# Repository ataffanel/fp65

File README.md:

# FP65: 65C02-based experimental computer platform

FP65 is a modular (retro)computer project based on the WDC65C02s.
It is mainly a playground to play and experiments with old computer technology and chips.

The design is modular in the sense that it is based on a backplane that carries the 65C02 memory bus.

The `FP` of *FP65* stands for *Front Panel*.
The original idea of the project is to build a front-panel controlable computer based on the 65C02.
Something very similar to the Altair 8800 or the IMSAI 8080.
The project has been a little bit side-tracked so far, but this is still one of the goal.

## Project goals and limitations

The main goal is to have fun with old computer technologies, learning new skils in the process in a nice side-effect.
In order to keep things fun and interesting, there needs to be some (artificial) limitations.

The focus so far has been to make a retro-inspired computer platform only using through-hole components that are still readily available (as of late 2023) at regular electronic retailer.
I could have sourced cool parts from ebay (and I am entertaining the idea for doing a 68K-based project), but here I really wanted to stick with easily and safely sourcable parts.
The only exception to this rule is the [USBIO-A](usbio-a/) board that uses an Arduino board to essencially emulate an Apple I keyboard and screen to USB-serial.

Within this focus, the spread of chip and design vintage is quite big: the modular backbone design is inspired by the later 70s computer kit like the Altair 8800 and the IMSAI 8080.
The main CPU, the WDC65C02s, is an improved CMOS version of the MOS6502 from the 80s. Similarly the SCSI-A 53C80 SCSI chip has its roots in the mid-80s.

The latest technologies so far are found in the SIO-A board that uses a 16C550 UART tranceiver, this chips is a late-80s chip but is very much reminecent of the 90s and early 2000s PC technology.
chance are, your current PC-compatible computer still has a 16550-compatible UART somewhere in the chipset.

Of course the memory used, be it static RAM or ROM (actually a FLASH chip), are also 90s to 2000s technologies: they are the latest generation still available as through-hole components.

## Boards

The board made so far are:
 - [Backplane](backplane/): 50-pins 4 boards backplane with power supply and chaining connectors
 - [MPU-A](mpu-a/): wdc65C02s CPU board with clock
 - [RAM-A](ram-a/): 32KBytes static ram
 - [ROM-A](rom-a/): 4KBytes to 24KBytes ROM. Implemented in a 128KBytes FLASH with 8 static pages (dip-switch selectable).
 - [SCSI-A](scsi-a/): Asynchronous 8bit SCSI-SC interface. SCSI2 compatible with internal and external MAC-style connector.
 - [SIO-A](sio-a/): 16C550 UART with RS232-level and TTS-level connection plus 65C22 VIA for Timer and parallel (GP)I/O
 - [USBIO-A](usbio-a/): APPLE-I style emulated I/O to a USB-serial port.

Most boards have been revised since the rev-A was produced.
Rev-Bs are implementation of the bodge wires fixes, they still need to be produced and tested.

# Software

FP65 has a memory map and I/O compatible with an apple-I (when using the USBIO-A board).
As such it can run WOZMON, the apple-I monitor, and any apple-I/replica-I software directly.

# License

All the board in this repos are licenced under the *CERN Open Hardware Licence Version 2 - Strongly Reciprocal* (CERN-OHL-S) license.

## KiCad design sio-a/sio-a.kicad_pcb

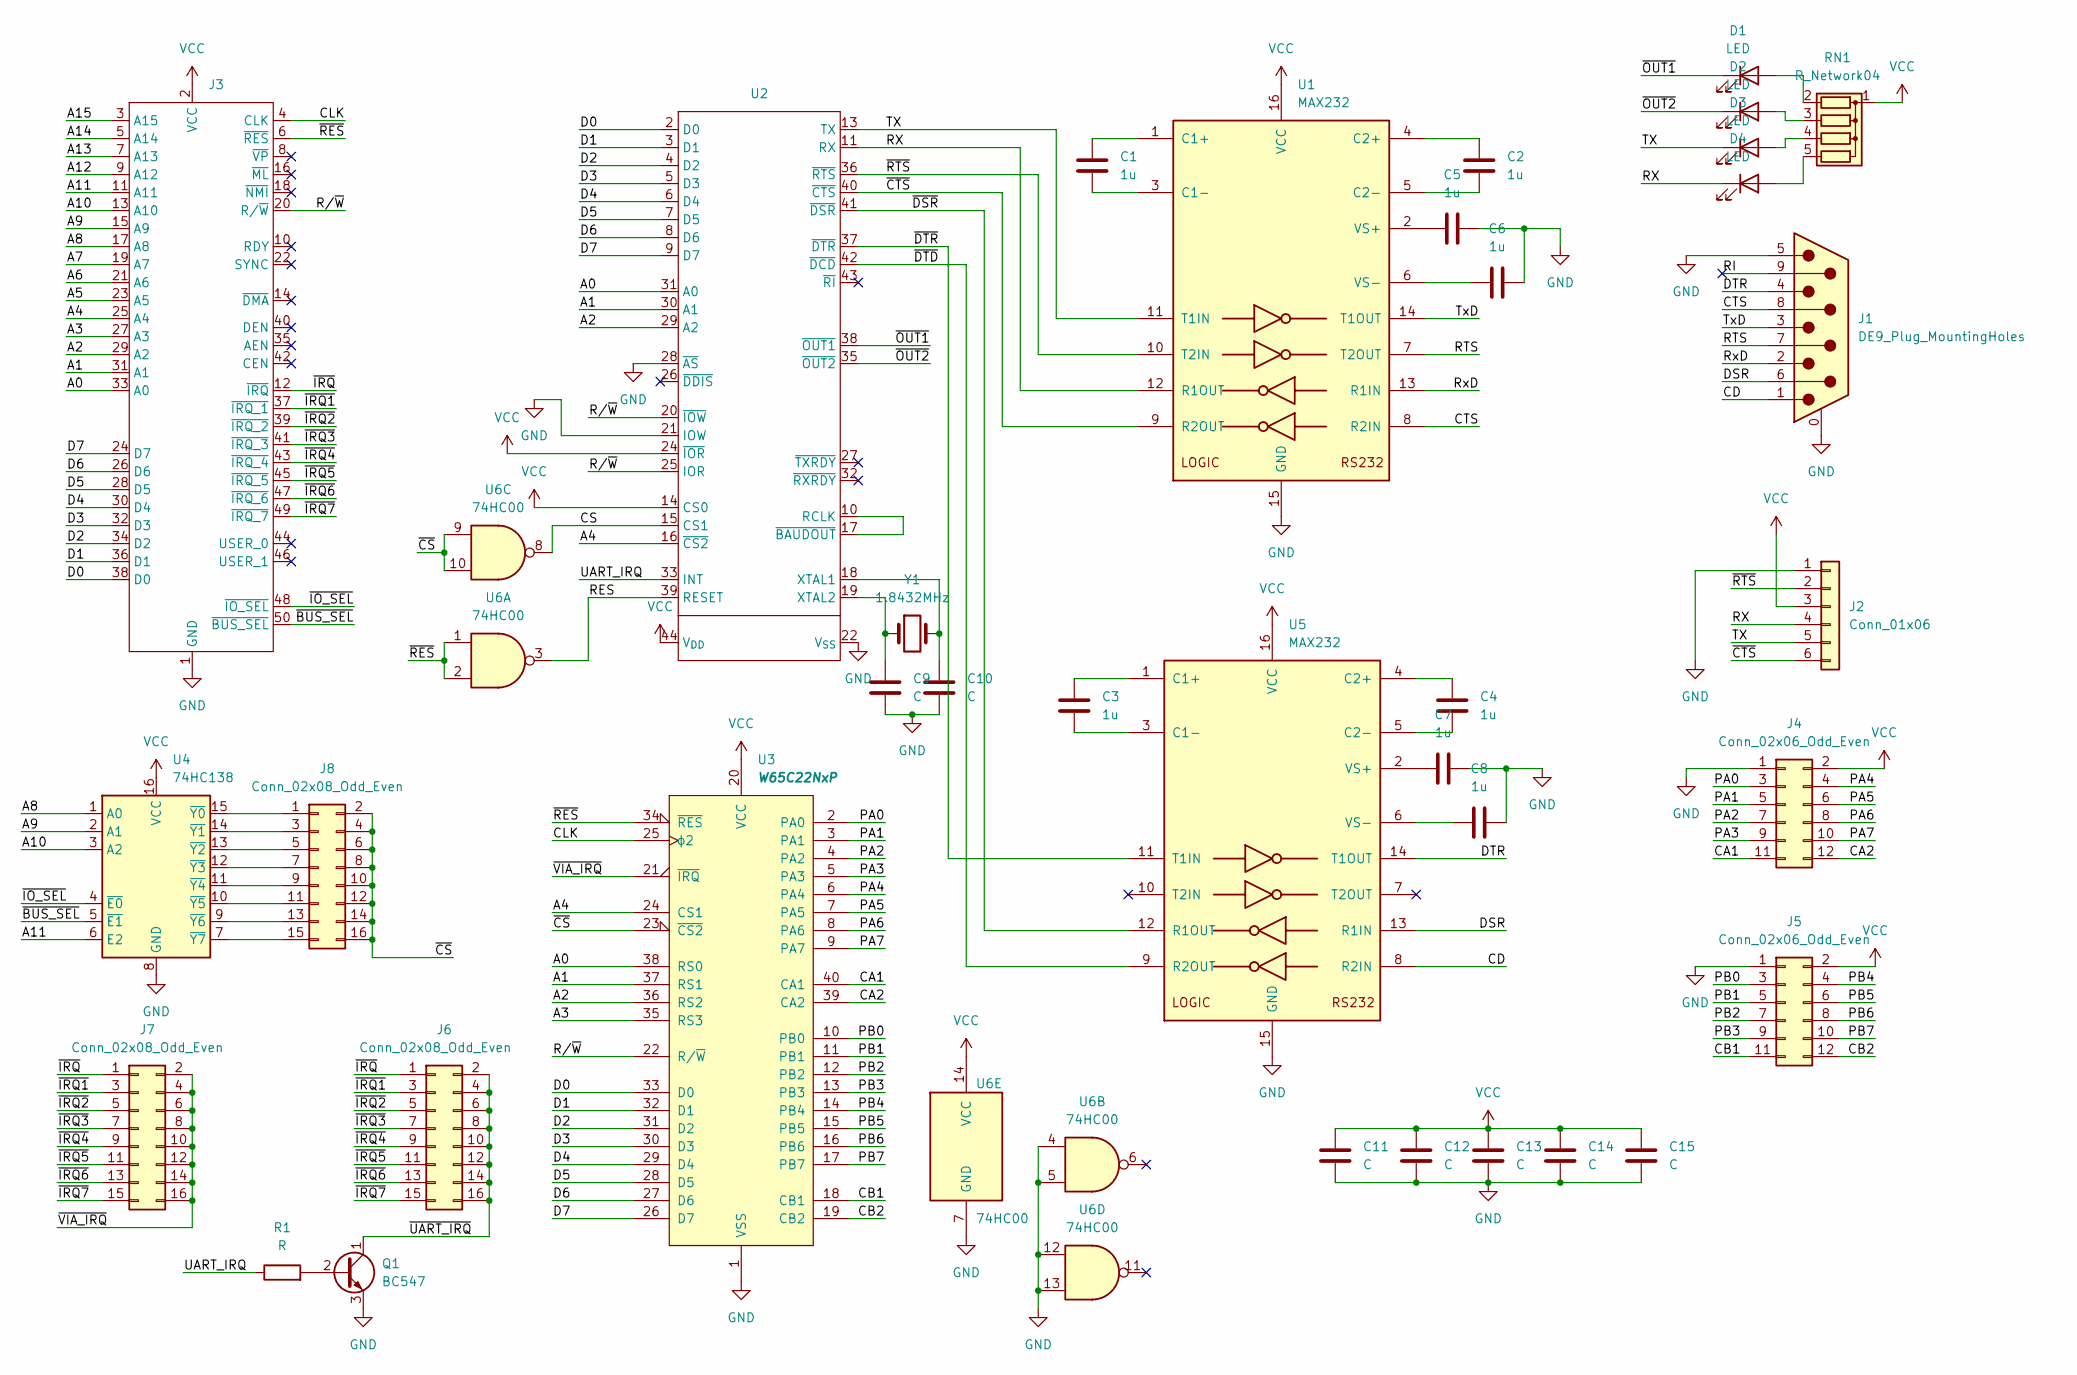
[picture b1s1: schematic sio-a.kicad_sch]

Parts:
C1, C2, C3, C4, C5, C6, C7, C8: 1u; C_Disc_D5.0mm_W2.5mm_P5.00mm
C9, C10, C11, C12, C13, C14, C15: C; C_Disc_D5.0mm_W2.5mm_P5.00mm
D1, D2, D3, D4: LED; LED_D3.0mm_Horizontal_O1.27mm_Z2.0mm
J1: DE9_Plug_MountingHoles; DSUB-9_Male_Horizontal_P2.77x2.84mm_EdgePinOffset9.90mm_Hou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
J2: Conn_01x06; PinHeader_1x06_P2.54mm_Horizontal
J3: PinHeader_2x25_P2.54mm_Horizontal
J4, J5: Conn_02x06_Odd_Even; PinHeader_2x06_P2.54mm_Vertical
J6, J7, J8: Conn_02x08_Odd_Even; PinHeader_2x08_P2.54mm_Vertical
Q1: BC547; TO-92_Inline
R1: R; R_Axial_DIN0207_L6.3mm_D2.5mm_P10.16mm_Horizontal
RN1: R_Network04; R_Array_SIP5
U1, U5: MAX232; DIP-16_W7.62mm
U2: PLCC-44_THT-Socket
U3: W65C22NxP; DIP-40_W15.24mm
U4: 74HC138; DIP-16_W7.62mm
U6: 74HC00; DIP-14_W7.62mm
Y1: 1.8432MHz; Crystal_HC49-U_Vertical

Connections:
/A0: J3.33 (A0), U2.31 (A0), U3.38 (RS0)
/A1: J3.31 (A1), U2.30 (A1), U3.37 (RS1)
/A2: J3.29 (A2), U2.29 (A2), U3.36 (RS2)
/A3: J3.27 (A3), U3.35 (RS3)
/A4: J3.25 (A4), U2.16 (~CS2), U3.24 (CS1)
/A5: J3.23 (A5)
/A6: J3.21 (A6)
/A7: J3.19 (A7)
/A8: J3.17 (A8), U4.1 (A0)
/A9: J3.15 (A9), U4.2 (A1)
/A10: J3.13 (A10), U4.3 (A2)
/A11: J3.11 (A11), U4.6 (E2)
/A12: J3.9 (A12)
/A13: J3.7 (A13)
/A14: J3.5 (A14)
/A15: J3.3 (A15)
/CA1: J4.11, U3.40 (CA1)
/CA2: J4.12, U3.39 (CA2)
/CB1: J5.11, U3.18 (CB1)
/CB2: J5.12, U3.19 (CB2)
/CD: J1.1, U5.8 (R2IN)
/CLK: J3.4 (CLK), U3.25 (ϕ2)
/CS: U2.15 (CS1), U6.8
/CTS: J1.8, U1.8 (R2IN)
/D0: J3.38 (D0), U2.2 (D0), U3.33 (D0)
/D1: J3.36 (D1), U2.3 (D1), U3.32 (D1)
/D2: J3.34 (D2), U2.4 (D2), U3.31 (D2)
/D3: J3.32 (D3), U2.5 (D3), U3.30 (D3)
/D4: J3.30 (D4), U2.6 (D4), U3.29 (D4)
/D5: J3.28 (D5), U2.7 (D5), U3.28 (D5)
/D6: J3.26 (D6), U2.8 (D6), U3.27 (D6)
/D7: J3.24 (D7), U2.9 (D7), U3.26 (D7)
/DSR: J1.6, U5.13 (R1IN)
/DTR: J1.4, U5.14 (T1OUT)
/PA0: J4.3, U3.2 (PA0)
/PA1: J4.5, U3.3 (PA1)
/PA2: J4.7, U3.4 (PA2)
/PA3: J4.9, U3.5 (PA3)
/PA4: J4.4, U3.6 (PA4)
/PA5: J4.6, U3.7 (PA5)
/PA6: J4.8, U3.8 (PA6)
/PA7: J4.10, U3.9 (PA7)
/PB0: J5.3, U3.10 (PB0)
/PB1: J5.5, U3.11 (PB1)
/PB2: J5.7, U3.12 (PB2)
/PB3: J5.9, U3.13 (PB3)
/PB4: J5.4, U3.14 (PB4)
/PB5: J5.6, U3.15 (PB5)
/PB6: J5.8, U3.16 (PB6)
/PB7: J5.10, U3.17 (PB7)
/RES: U2.39 (RESET), U6.3
/RI: J1.9
/RTS: J1.7, U1.7 (T2OUT)
/RX: D4.1 (K), J2.4, U1.12 (R1OUT), U2.11 (RX)
/RxD: J1.2, U1.13 (R1IN)
/R/~W: J3.20 (R/~W), U2.20 (~IOW), U2.25 (IOR), U3.22 (R/~W)
/TX: D3.1 (K), J2.5, U1.11 (T1IN), U2.13 (TX)
/TxD: J1.3, U1.14 (T1OUT)
/UART_IRQ: R1.1, U2.33 (INT)
/~BUS_SEL: J3.50 (~BUS_SEL), U4.5 (~E1)
/~CS: J8.2, J8.4, J8.6, J8.8, J8.10, J8.12, J8.14, J8.16, U3.23 (~CS2), U6.9, U6.10
/~CTS: J2.6, U1.9 (R2OUT), U2.40 (~CTS)
/~DSR: U2.41 (~DSR), U5.12 (R1OUT)
/~DTD: U2.42 (~DCD), U5.9 (R2OUT)
/~DTR: U2.37 (~DTR), U5.11 (T1IN)
/~IO_SEL: J3.48 (~IO_SEL), U4.4 (~E0)
/~IRQ1: J3.37 (~IRQ_1), J6.3, J7.3
/~IRQ2: J3.39 (~IRQ_2), J6.5, J7.5
/~IRQ3: J3.41 (~IRQ_3), J6.7, J7.7
/~IRQ4: J3.43 (~IRQ_4), J6.9, J7.9
/~IRQ5: J3.45 (~IRQ_5), J6.11, J7.11
/~IRQ6: J3.47 (~IRQ_6), J6.13, J7.13
/~IRQ7: J3.49 (~IRQ_7), J6.15, J7.15
/~IRQ: J3.12 (~IRQ), J6.1, J7.1
/~OUT1: D1.1 (K), U2.38 (~OUT1)
/~OUT2: D2.1 (K), U2.35 (~OUT2)
/~RES: J3.6 (~RES), U3.34 (~RES), U6.1, U6.2
/~RTS: J2.2, U1.10 (T2IN), U2.36 (~RTS)
/~UART_IRQ: J6.2, J6.4, J6.6, J6.8, J6.10, J6.12, J6.14, J6.16, Q1.1 (C)
/~VIA_IRQ: J7.2, J7.4, J7.6, J7.8, J7.10, J7.12, J7.14, J7.16, U3.21 (~IRQ)
GND: C5.2, C6.2, C7.1, C8.2, C9.2, C10.2, C11.2, C12.2, C13.2, C14.2, C15.2, J1.0 (PAD), J1.5, J2.1, J3.1 (GND), J4.1, J5.1, Q1.3 (E), U1.15 (GND), U2.21 (IOW), U2.22 (V_{SS}), U2.28 (~AS), U3.1 (VSS), U4.8 (GND), U5.15 (GND), U6.4, U6.5, U6.7 (GND), U6.12, U6.13
unnamed: D1.2 (A), RN1.2 (R1)
unnamed: D2.2 (A), RN1.3 (R2)
unnamed: D3.2 (A), RN1.4 (R3)
unnamed: D4.2 (A), RN1.5 (R4)
unnamed: J8.1, U4.15 (~Y0)
unnamed: J8.3, U4.14 (~Y1)
unnamed: J8.5, U4.13 (~Y2)
unnamed: J8.7, U4.12 (~Y3)
unnamed: J8.9, U4.11 (~Y4)
unnamed: J8.11, U4.10 (~Y5)
unnamed: J8.13, U4.9 (~Y6)
unnamed: J8.15, U4.7 (~Y7)
unnamed: Q1.2 (B), R1.2
unnamed: C1.1, U1.1 (C1+)
unnamed: C1.2, U1.3 (C1-)
unnamed: C2.1, U1.4 (C2+)
unnamed: C2.2, U1.5 (C2-)
unnamed: C5.1, U1.2 (VS+)
unnamed: C6.1, U1.6 (VS-)
unnamed: U2.10 (RCLK), U2.17 (~BAUDOUT)
unnamed: C10.1, U2.18 (XTAL1), Y1.2
unnamed: C9.1, U2.19 (XTAL2), Y1.1
unnamed: C3.1, U5.1 (C1+)
unnamed: C3.2, U5.3 (C1-)
unnamed: C4.1, U5.4 (C2+)
unnamed: C4.2, U5.5 (C2-)
unnamed: C7.2, U5.2 (VS+)
unnamed: C8.1, U5.6 (VS-)
VCC: C11.1, C12.1, C13.1, C14.1, C15.1, J2.3, J3.2 (VCC), J4.2, J5.2, RN1.1 (common), U1.16 (VCC), U2.14 (CS0), U2.24 (~IOR), U2.44 (V_{DD}), U3.20 (VCC), U4.16 (VCC), U5.16 (VCC), U6.14 (VCC)

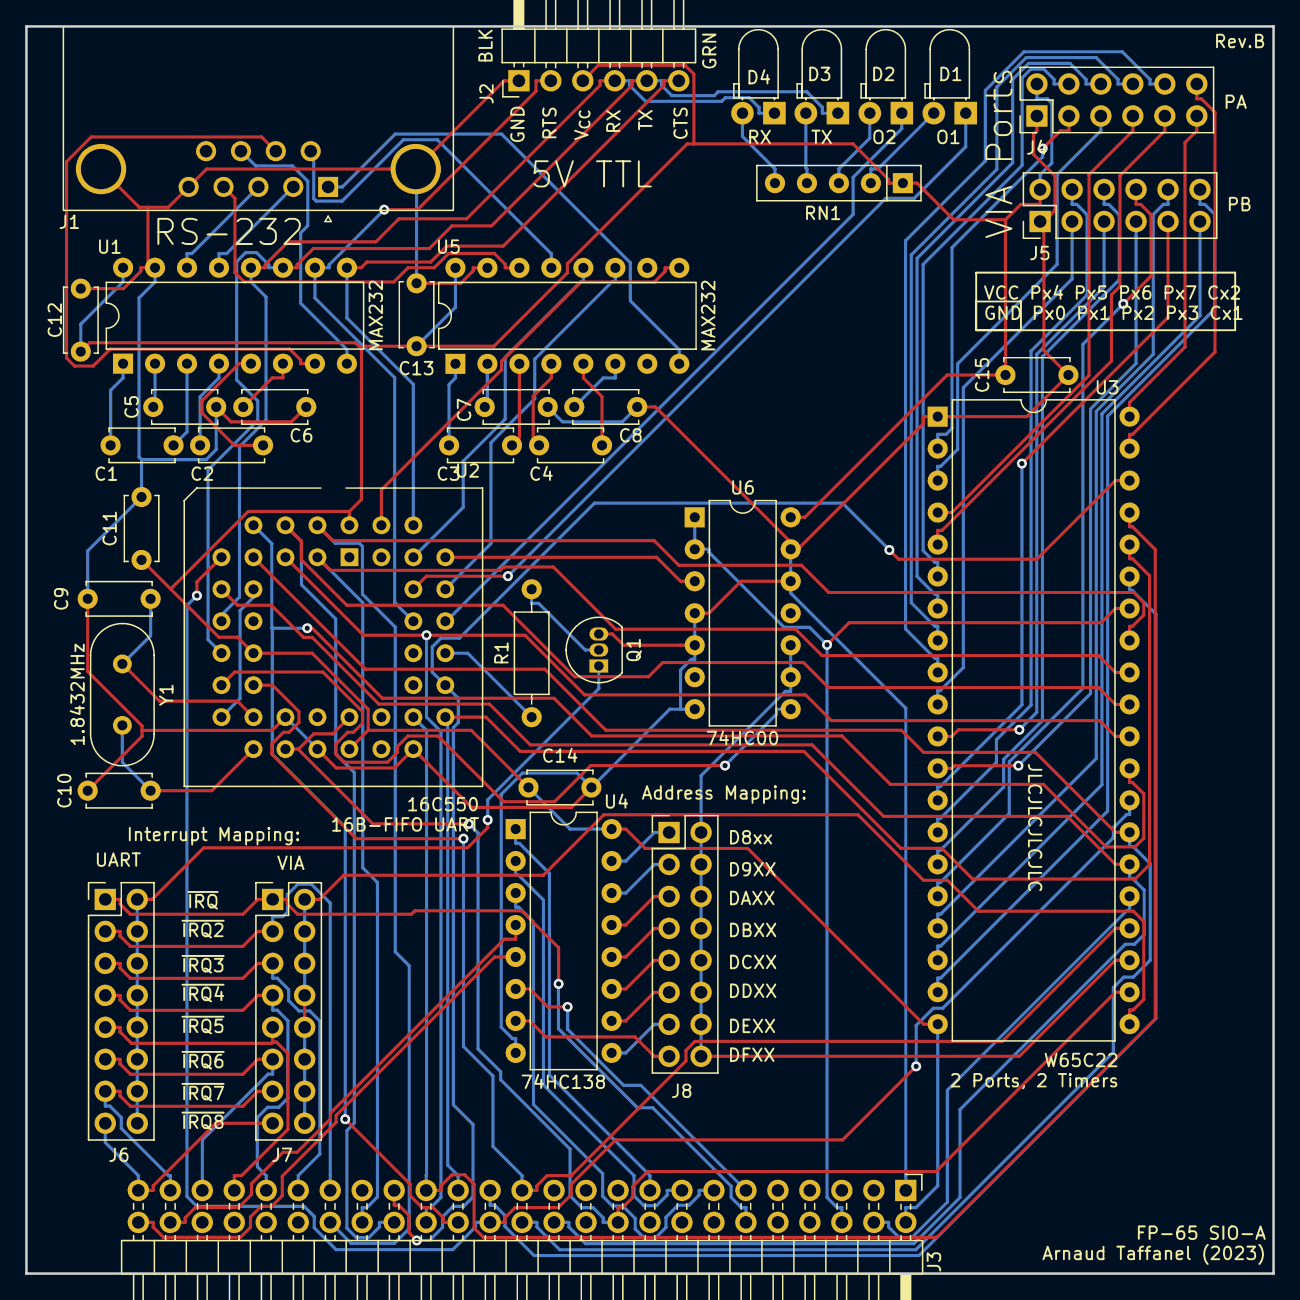
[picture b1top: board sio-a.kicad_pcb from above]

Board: 2 copper layers, 99.1 x 99.1 mm, 37 parts (0 on the bottom side), 102 nets.

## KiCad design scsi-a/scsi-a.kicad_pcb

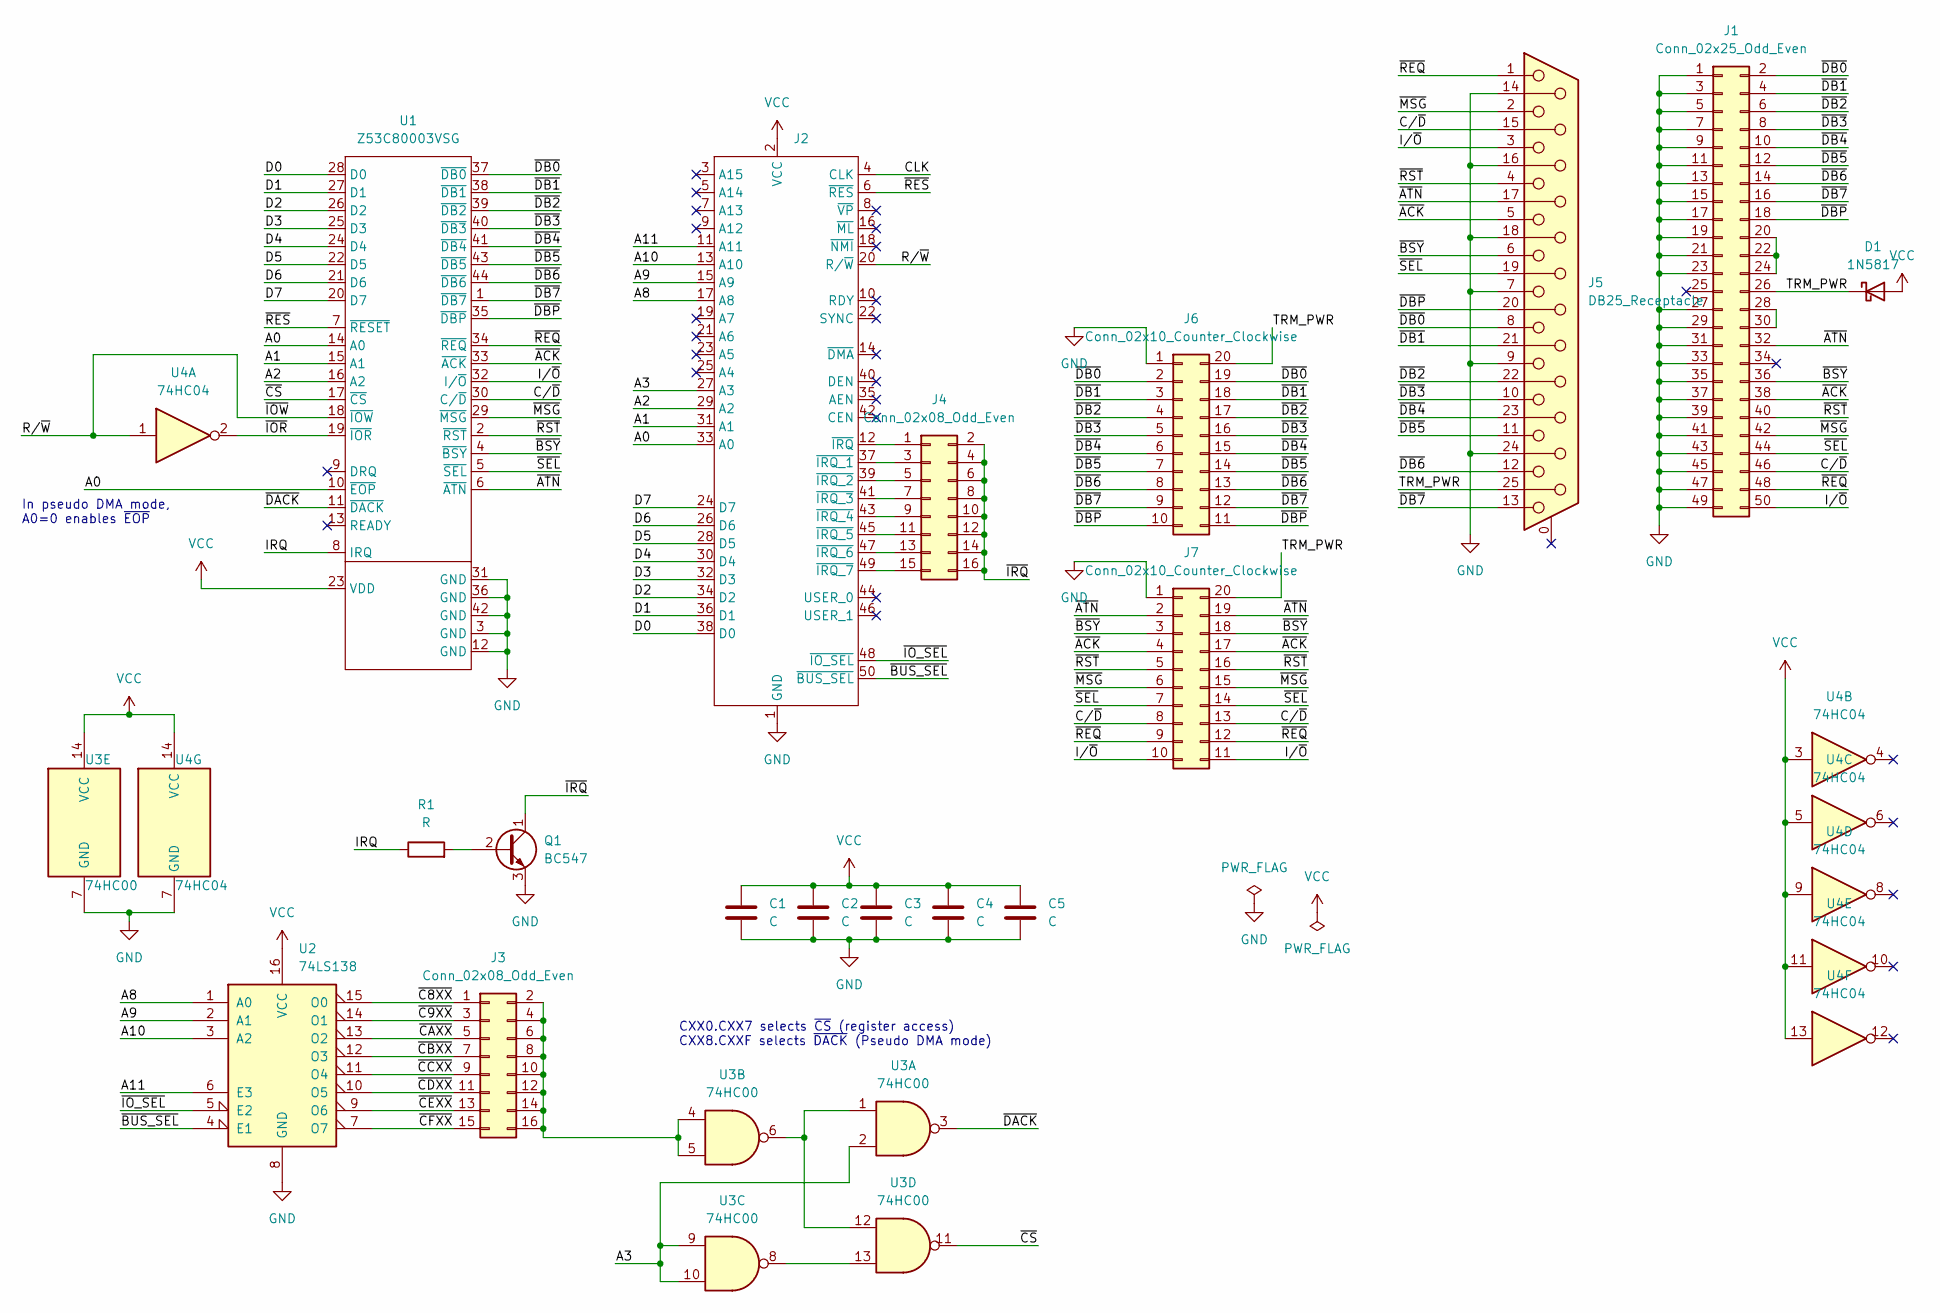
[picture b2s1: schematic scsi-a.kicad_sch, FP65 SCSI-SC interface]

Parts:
C1, C2, C3, C5: C; C_Disc_D5.0mm_W2.5mm_P5.00mm
C4: C; CP_Radial_D5.0mm_P2.00mm
D1: 1N5817; D_DO-41_SOD81_P10.16mm_Horizontal
J1: Conn_02x25_Odd_Even; IDC-Header_2x25_P2.54mm_Horizontal
J2: PinHeader_2x25_P2.54mm_Horizontal
J3, J4: Conn_02x08_Odd_Even; PinHeader_2x08_P2.54mm_Vertical
J5: DB25_Receptacle; DSUB-25_Female_Horizontal_P2.77x2.84mm_EdgePinOffset9.90mm_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
J6, J7: Conn_02x10_Counter_Clockwise; DIP-20_W7.62mm_Socket
Q1: BC547; TO-92_Inline
R1: R; R_Axial_DIN0204_L3.6mm_D1.6mm_P7.62mm_Horizontal
U1: Z53C80003VSG; PLCC-44_THT-Socket
U2: 74LS138; DIP-16_W7.62mm
U3: 74HC00; DIP-14_W7.62mm
U4: 74HC04; DIP-14_W7.62mm

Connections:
/A0: J2.33 (A0), U1.10 (~EOP), U1.14 (A0)
/A1: J2.31 (A1), U1.15 (A1)
/A2: J2.29 (A2), U1.16 (A2)
/A3: J2.27 (A3), U3.2, U3.9, U3.10
/A8: J2.17 (A8), U2.1 (A0)
/A9: J2.15 (A9), U2.2 (A1)
/A10: J2.13 (A10), U2.3 (A2)
/A11: J2.11 (A11), U2.6 (E3)
/CLK: J2.4 (CLK)
/C/~D: J1.46, J5.15, J7.8, J7.13, U1.30 (C/~D)
/D0: J2.38 (D0), U1.28 (D0)
/D1: J2.36 (D1), U1.27 (D1)
/D2: J2.34 (D2), U1.26 (D2)
/D3: J2.32 (D3), U1.25 (D3)
/D4: J2.30 (D4), U1.24 (D4)
/D5: J2.28 (D5), U1.22 (D5)
/D6: J2.26 (D6), U1.21 (D6)
/D7: J2.24 (D7), U1.20 (D7)
/IRQ: R1.1, U1.8 (IRQ)
/I/~O: J1.50, J5.3, J7.10, J7.11, U1.32 (I/~O)
/R/~W: J2.20 (R/~W), U1.18 (~IOW), U4.1
/TRM_PWR: D1.1 (K), J1.26, J5.25, J6.20, J7.20
/~ACK: J1.38, J5.5, J7.4, J7.17, U1.33 (~ACK)
/~ATN: J1.32, J5.17, J7.2, J7.19, U1.6 (~ATN)
/~BSY: J1.36, J5.6, J7.3, J7.18, U1.4 (~BSY)
/~BUS_SEL: J2.50 (~BUS_SEL), U2.4 (E1)
/~C8XX: J3.1, U2.15 (O0)
/~C9XX: J3.3, U2.14 (O1)
/~CAXX: J3.5, U2.13 (O2)
/~CBXX: J3.7, U2.12 (O3)
/~CCXX: J3.9, U2.11 (O4)
/~CDXX: J3.11, U2.10 (O5)
/~CEXX: J3.13, U2.9 (O6)
/~CFXX: J3.15, U2.7 (O7)
/~CS: U1.17 (~CS), U3.11
/~DACK: U1.11 (~DACK), U3.3
/~DB0: J1.2, J5.8, J6.2, J6.19, U1.37 (~DB0)
/~DB1: J1.4, J5.21, J6.3, J6.18, U1.38 (~DB1)
/~DB2: J1.6, J5.22, J6.4, J6.17, U1.39 (~DB2)
/~DB3: J1.8, J5.10, J6.5, J6.16, U1.40 (~DB3)
/~DB4: J1.10, J5.23, J6.6, J6.15, U1.41 (~DB4)
/~DB5: J1.12, J5.11, J6.7, J6.14, U1.43 (~DB5)
/~DB6: J1.14, J5.12, J6.8, J6.13, U1.44 (~DB6)
/~DB7: J1.16, J5.13, J6.9, J6.12, U1.1 (~DB7)
/~DBP: J1.18, J5.20, J6.10, J6.11, U1.35 (~DBP)
/~IOR: U1.19 (~IOR), U4.2
/~IO_SEL: J2.48 (~IO_SEL), U2.5 (E2)
/~IRQ: J4.2, J4.4, J4.6, J4.8, J4.10, J4.12, J4.14, J4.16, Q1.1 (C)
/~MSG: J1.42, J5.2, J7.6, J7.15, U1.29 (~MSG)
/~REQ: J1.48, J5.1, J7.9, J7.12, U1.34 (~REQ)
/~RES: J2.6 (~RES), U1.7 (~RESET)
/~RST: J1.40, J5.4, J7.5, J7.16, U1.2 (~RST)
/~SEL: J1.44, J5.19, J7.7, J7.14, U1.5 (~SEL)
GND: C1.2, C2.2, C3.2, C4.2, C5.2, J1.1, J1.3, J1.5, J1.7, J1.9, J1.11, J1.13, J1.15, J1.17, J1.19, J1.21, J1.23, J1.27, J1.29, J1.31, J1.33, J1.35, J1.37, J1.39, J1.41, J1.43, J1.45, J1.47, J1.49, J2.1 (GND), J5.7, J5.9, J5.14, J5.16, J5.18, J5.24, J6.1, J7.1, Q1.3 (E), U1.3 (GND), U1.12 (GND), U1.31 (GND), U1.36 (GND), U1.42 (GND), U2.8 (GND), U3.7 (GND), U4.7 (GND)
unnamed: J1.20, J1.22, J1.24
unnamed: J1.28, J1.30
unnamed: J2.37 (~IRQ_1), J4.3
unnamed: J2.39 (~IRQ_2), J4.5
unnamed: J2.41 (~IRQ_3), J4.7
unnamed: J2.43 (~IRQ_4), J4.9
unnamed: J2.45 (~IRQ_5), J4.11
unnamed: J2.47 (~IRQ_6), J4.13
unnamed: J2.49 (~IRQ_7), J4.15
unnamed: J2.12 (~IRQ), J4.1
unnamed: J3.2, J3.4, J3.6, J3.8, J3.10, J3.12, J3.14, J3.16, U3.4, U3.5
unnamed: Q1.2 (B), R1.2
unnamed: U3.1, U3.6, U3.12
unnamed: U3.8, U3.13
VCC: C1.1, C2.1, C3.1, C4.1, C5.1, D1.2 (A), J2.2 (VCC), U1.23 (VDD), U2.16 (VCC), U3.14 (VCC), U4.3, U4.5, U4.9, U4.11, U4.13, U4.14 (VCC)

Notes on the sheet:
CXX0.CXX7 selects ~{CS} (register access) CXX8.CXXF selects ~{DACK} (Pseudo DMA mode)
In pseudo DMA mode, A0=0 enables ~{EOP}

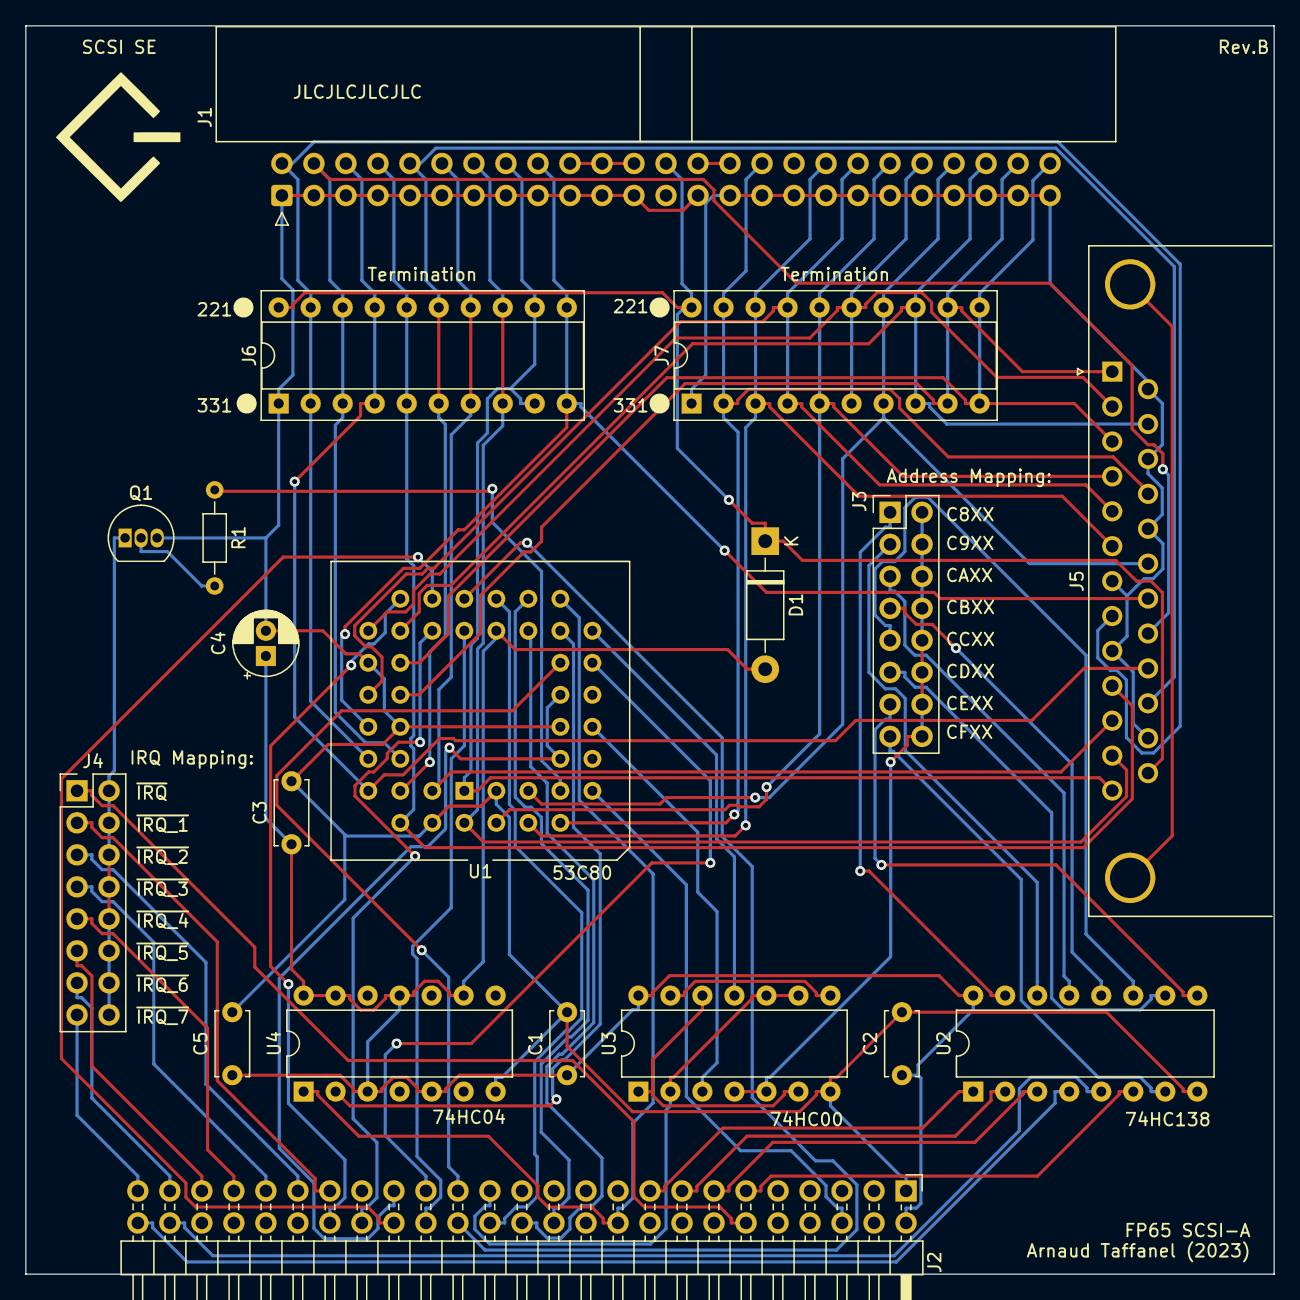
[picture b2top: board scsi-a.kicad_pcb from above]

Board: 2 copper layers, 99.1 x 99.1 mm, 19 parts (0 on the bottom side), 68 nets.

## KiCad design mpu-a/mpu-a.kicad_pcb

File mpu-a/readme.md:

# wdc65C02s CPU board with clock

CPU board for the 65C02.

Implements support for a crystall oscillator and connector and logic for a front-pannel to access the CPU data line even when isolated from the backplane.

Also generates an enable signal for selecting the IO pages at ```$Cxxx```.

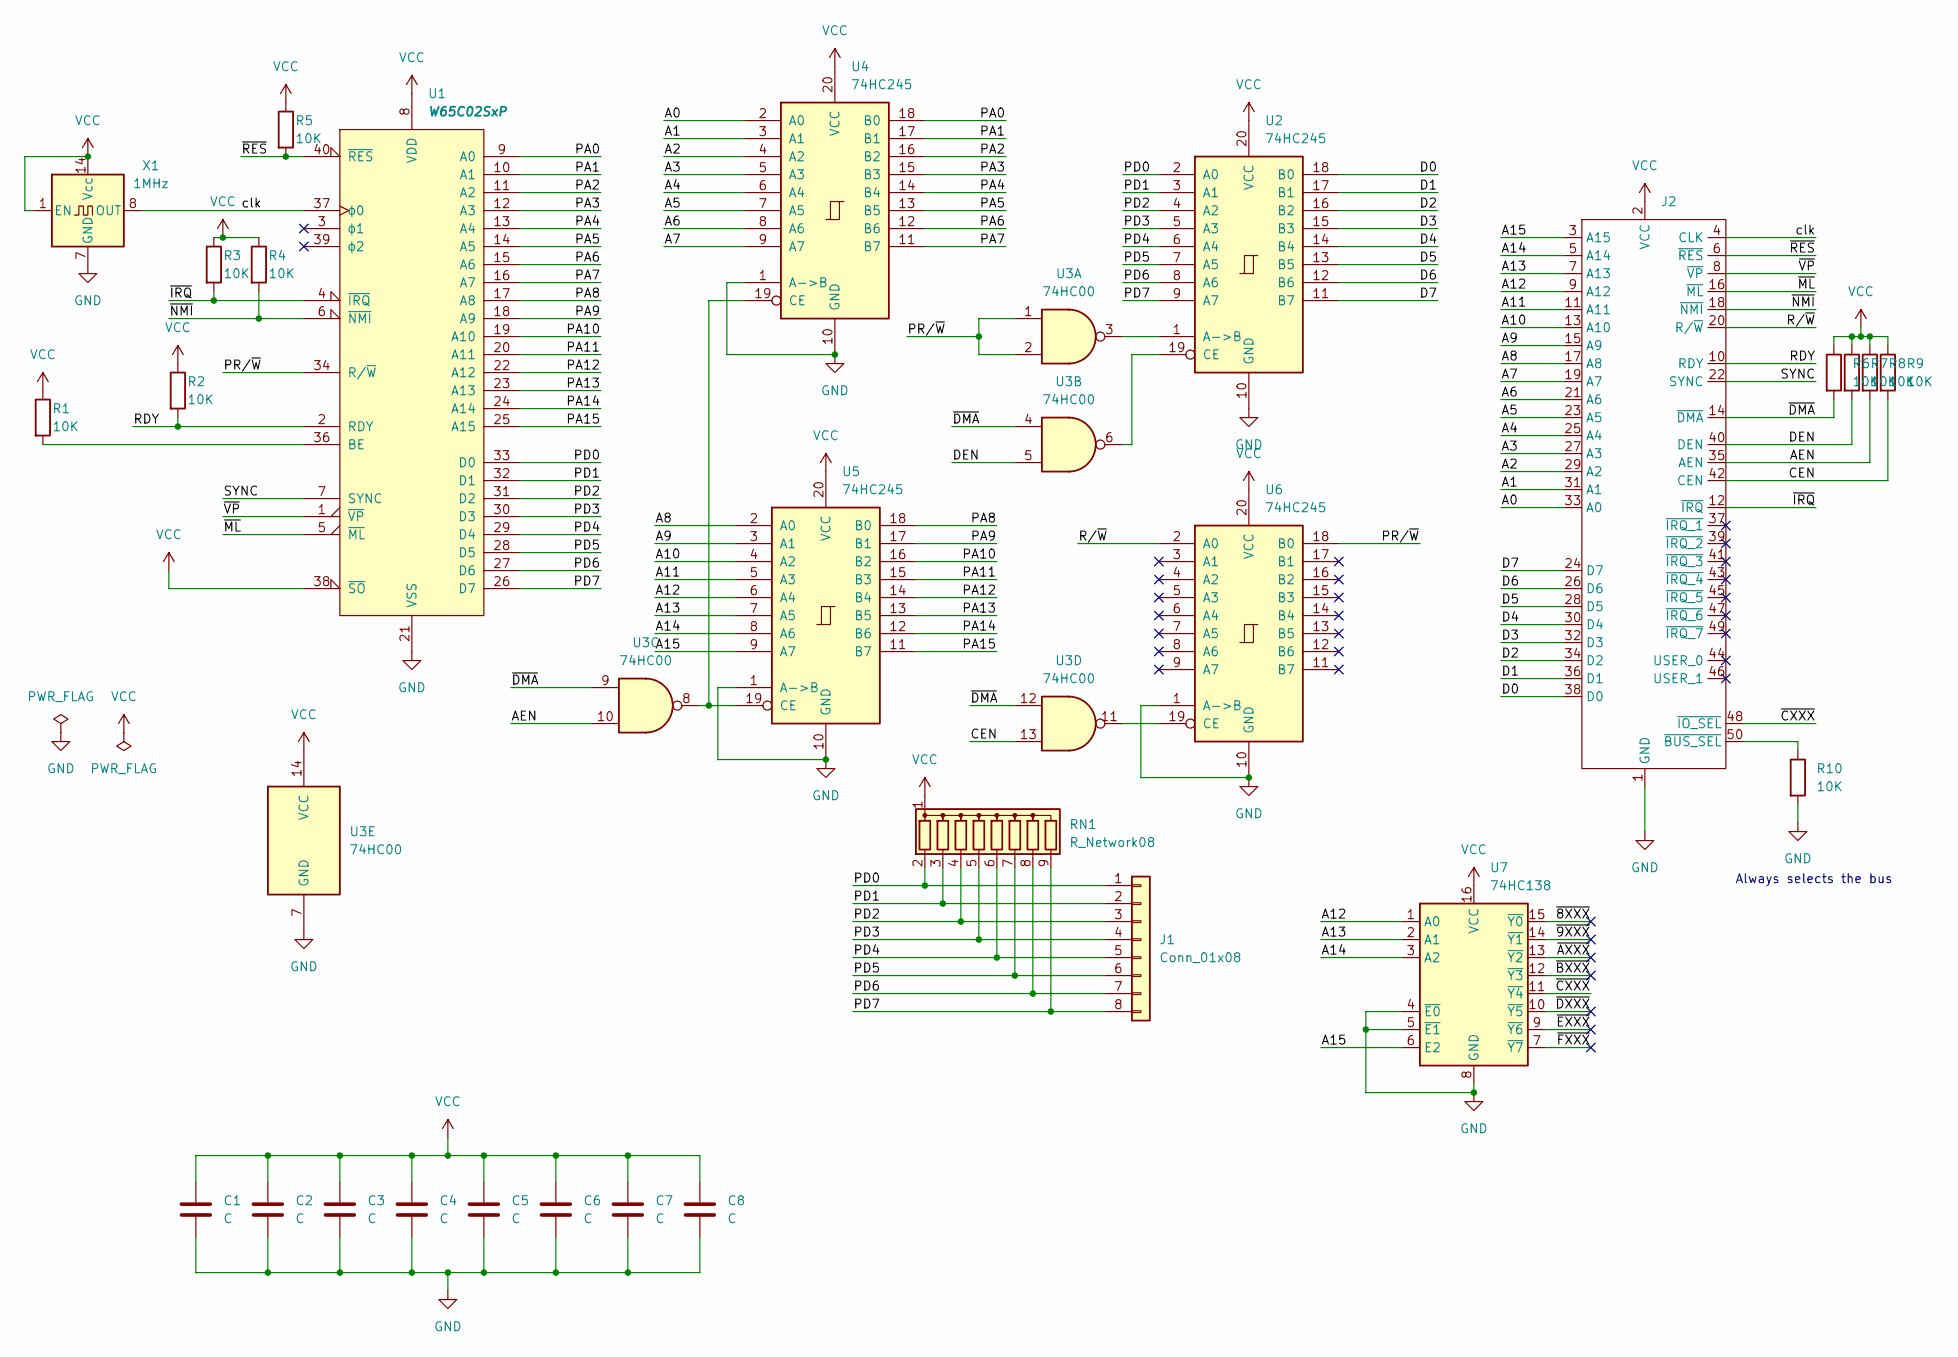
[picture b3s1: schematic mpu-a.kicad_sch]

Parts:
C1, C2, C3, C4, C5, C6, C7, C8: C; C_Disc_D4.3mm_W1.9mm_P5.00mm
J1: Conn_01x08; PinHeader_2x04_P2.54mm_Vertical
J2: PinHeader_2x25_P2.54mm_Horizontal
R1, R2, R3, R4, R5, R6, R7, R8, R9, R10: 10K; R_Axial_DIN0204_L3.6mm_D1.6mm_P7.62mm_Horizontal
RN1: R_Network08; R_Array_SIP9
U1: W65C02SxP; DIP-40_W15.24mm
U2, U4, U5, U6: 74HC245; DIP-20_W7.62mm
U3: 74HC00; DIP-14_W7.62mm
U7: 74HC138; DIP-16_W7.62mm
X1: 1MHz; Oscillator_DIP-14

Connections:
/A0: J2.33 (A0), U4.2 (A0)
/A1: J2.31 (A1), U4.3 (A1)
/A2: J2.29 (A2), U4.4 (A2)
/A3: J2.27 (A3), U4.5 (A3)
/A4: J2.25 (A4), U4.6 (A4)
/A5: J2.23 (A5), U4.7 (A5)
/A6: J2.21 (A6), U4.8 (A6)
/A7: J2.19 (A7), U4.9 (A7)
/A8: J2.17 (A8), U5.2 (A0)
/A9: J2.15 (A9), U5.3 (A1)
/A10: J2.13 (A10), U5.4 (A2)
/A11: J2.11 (A11), U5.5 (A3)
/A12: J2.9 (A12), U5.6 (A4), U7.1 (A0)
/A13: J2.7 (A13), U5.7 (A5), U7.2 (A1)
/A14: J2.5 (A14), U5.8 (A6), U7.3 (A2)
/A15: J2.3 (A15), U5.9 (A7), U7.6 (E2)
/AEN: J2.35 (AEN), R8.2, U3.10
/CEN: J2.42 (CEN), R9.2, U3.13
/D0: J2.38 (D0), U2.18 (B0)
/D1: J2.36 (D1), U2.17 (B1)
/D2: J2.34 (D2), U2.16 (B2)
/D3: J2.32 (D3), U2.15 (B3)
/D4: J2.30 (D4), U2.14 (B4)
/D5: J2.28 (D5), U2.13 (B5)
/D6: J2.26 (D6), U2.12 (B6)
/D7: J2.24 (D7), U2.11 (B7)
/DEN: J2.40 (DEN), R7.2, U3.5
/PA0: U1.9 (A0), U4.18 (B0)
/PA1: U1.10 (A1), U4.17 (B1)
/PA2: U1.11 (A2), U4.16 (B2)
/PA3: U1.12 (A3), U4.15 (B3)
/PA4: U1.13 (A4), U4.14 (B4)
/PA5: U1.14 (A5), U4.13 (B5)
/PA6: U1.15 (A6), U4.12 (B6)
/PA7: U1.16 (A7), U4.11 (B7)
/PA8: U1.17 (A8), U5.18 (B0)
/PA9: U1.18 (A9), U5.17 (B1)
/PA10: U1.19 (A10), U5.16 (B2)
/PA11: U1.20 (A11), U5.15 (B3)
/PA12: U1.22 (A12), U5.14 (B4)
/PA13: U1.23 (A13), U5.13 (B5)
/PA14: U1.24 (A14), U5.12 (B6)
/PA15: U1.25 (A15), U5.11 (B7)
/PD0: J1.1, RN1.2 (R1), U1.33 (D0), U2.2 (A0)
/PD1: J1.2, RN1.3 (R2), U1.32 (D1), U2.3 (A1)
/PD2: J1.3, RN1.4 (R3), U1.31 (D2), U2.4 (A2)
/PD3: J1.4, RN1.5 (R4), U1.30 (D3), U2.5 (A3)
/PD4: J1.5, RN1.6 (R5), U1.29 (D4), U2.6 (A4)
/PD5: J1.6, RN1.7 (R6), U1.28 (D5), U2.7 (A5)
/PD6: J1.7, RN1.8 (R7), U1.27 (D6), U2.8 (A6)
/PD7: J1.8, RN1.9 (R8), U1.26 (D7), U2.9 (A7)
/PR/~W: U1.34 (R/~W), U3.1, U3.2, U6.18 (B0)
/RDY: J2.10 (RDY), R2.2, U1.2 (RDY)
/R/~W: J2.20 (R/~W), U6.2 (A0)
/SYNC: J2.22 (SYNC), U1.7 (SYNC)
/clk: J2.4 (CLK), U1.37 (ϕ0), X1.8 (OUT)
/~8XXX: U7.15 (~Y0)
/~9XXX: U7.14 (~Y1)
/~AXXX: U7.13 (~Y2)
/~BXXX: U7.12 (~Y3)
/~CXXX: J2.48 (~IO_SEL), U7.11 (~Y4)
/~DMA: J2.14 (~DMA), R6.2, U3.4, U3.9, U3.12
/~DXXX: U7.10 (~Y5)
/~EXXX: U7.9 (~Y6)
/~FXXX: U7.7 (~Y7)
/~IRQ: J2.12 (~IRQ), R3.2, U1.4 (~IRQ)
/~ML: J2.16 (~ML), U1.5 (~ML)
/~NMI: J2.18 (~NMI), R4.2, U1.6 (~NMI)
/~RES: J2.6 (~RES), R5.2, U1.40 (~RES)
/~VP: J2.8 (~VP), U1.1 (~VP)
GND: C1.2, C2.2, C3.2, C4.2, C5.2, C6.2, C7.2, C8.2, J2.1 (GND), R10.2, U1.21 (VSS), U2.10 (GND), U3.7 (GND), U4.1 (A->B), U4.10 (GND), U5.1 (A->B), U5.10 (GND), U6.1 (A->B), U6.10 (GND), U7.4 (~E0), U7.5 (~E1), U7.8 (GND), X1.7 (GND)
unnamed: J2.50 (~BUS_SEL), R10.1
unnamed: R1.2, U1.36 (BE)
unnamed: U2.1 (A->B), U3.3
unnamed: U2.19 (CE), U3.6
unnamed: U3.8, U4.19 (CE), U5.19 (CE)
unnamed: U3.11, U6.19 (CE)
VCC: C1.1, C2.1, C3.1, C4.1, C5.1, C6.1, C7.1, C8.1, J2.2 (VCC), R1.1, R2.1, R3.1, R4.1, R5.1, R6.1, R7.1, R8.1, R9.1, RN1.1 (common), U1.8 (VDD), U1.38 (~SO), U2.20 (VCC), U3.14 (VCC), U4.20 (VCC), U5.20 (VCC), U6.20 (VCC), U7.16 (VCC), X1.1 (EN), X1.14 (Vcc)

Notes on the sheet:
Always selects the bus

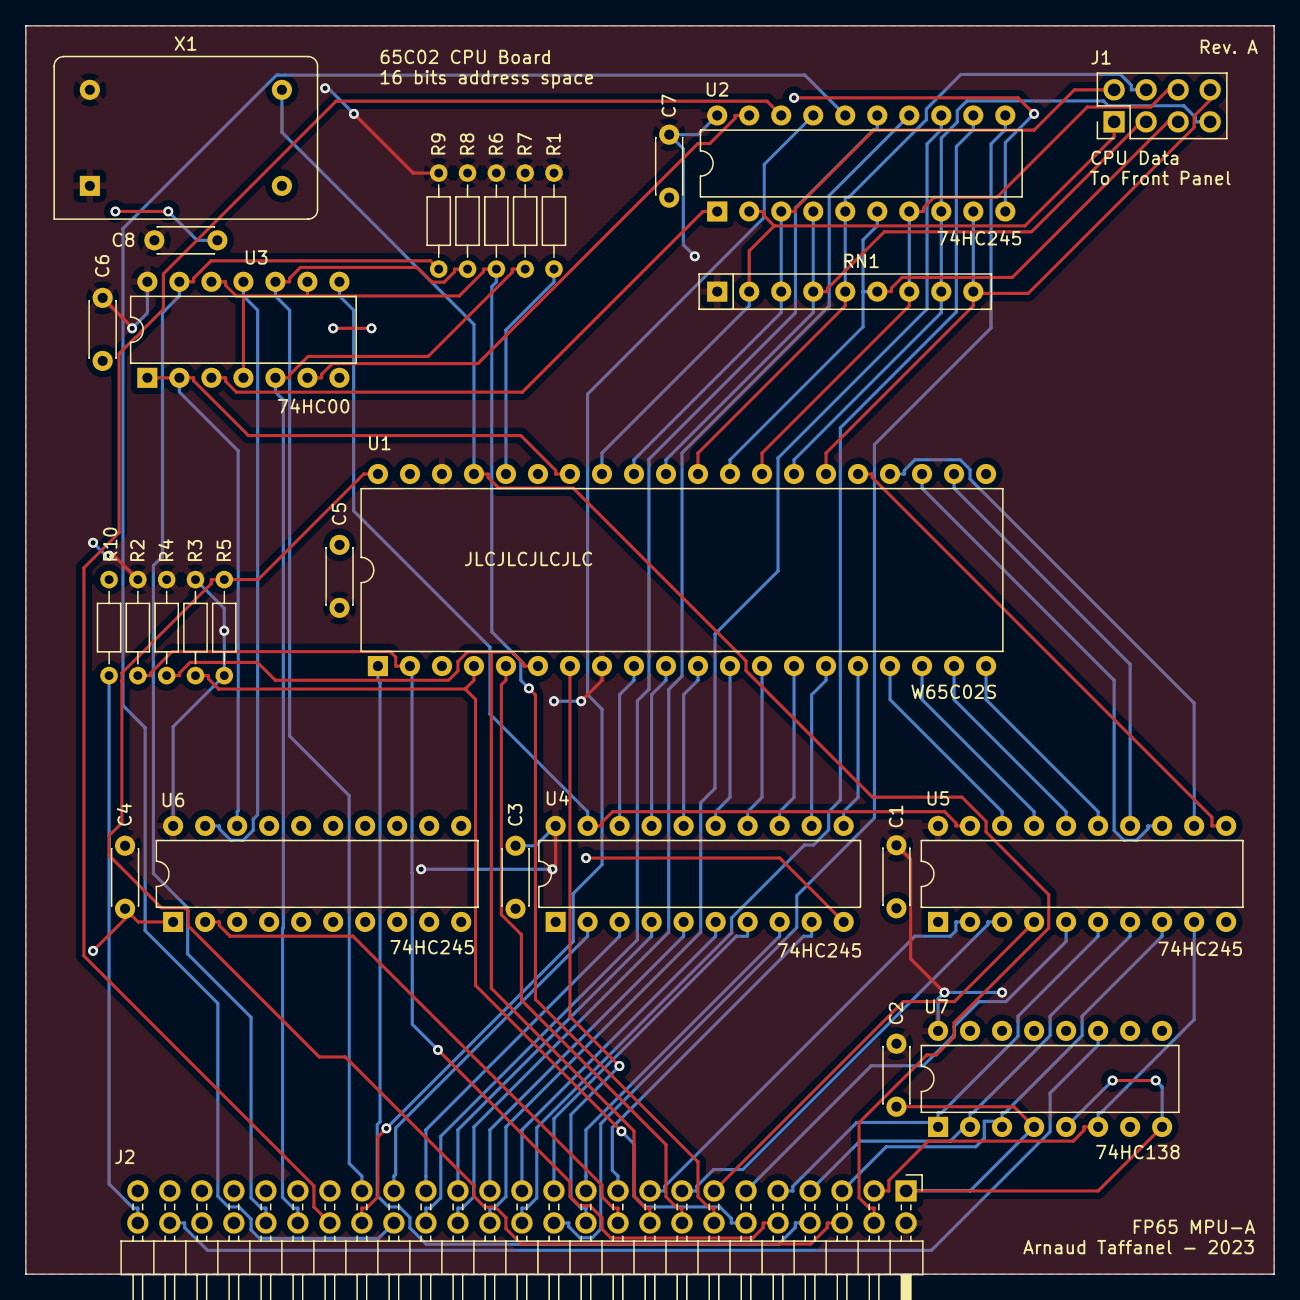
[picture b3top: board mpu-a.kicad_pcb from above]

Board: 2 copper layers, 99.1 x 99.1 mm, 29 parts (0 on the bottom side), 71 nets.
